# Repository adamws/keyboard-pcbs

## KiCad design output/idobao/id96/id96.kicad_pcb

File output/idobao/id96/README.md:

## idobao/id96

[layout](id96-kle.json) - [PCB](id96.kicad_pcb)

{:loading="lazy"}

[Open in keyboard-layout-editor](http://www.keyboard-layout-editor.com/##@@_x:2.75&c=#777777;&=5,0&_c=#cccccc;&=5,1&=5,2&=5,3&=5,4&=5,5&=5,6&=5,7&=5,8&=11,8&=11,7&=11,5&=11,4&_c=#aaaaaa;&=11,3&=11,6&=11,2&=11,1&=11,0&=6,3;&@_x:2.75&c=#cccccc;&=4,0&=4,1&=4,2&=4,3&=4,4&=4,5&=4,6&=4,7&=4,8&=10,8&=10,7&=10,5&=10,4&_c=#aaaaaa&w:2;&=10,6%0A%0A%0A0,0&_c=#777777;&=10,2&_c=#aaaaaa;&=10,1&=10,0&=6,4;&@_x:2.75&w:1.5;&=3,0&_c=#cccccc;&=3,1&=3,2&=3,3&=3,4&=3,5&=3,6&=3,7&=3,8&=9,8&=9,7&=9,5&=9,4&_w:1.5;&=8,4&=9,6&=9,2&=9,1&_c=#aaaaaa&h:2;&=8,0%0A%0A%0A1,0;&@_x:2.75&c=#777777&w:1.75;&=2,0&_c=#cccccc;&=2,1&=2,2&=2,3&=2,4&=2,5&=2,6&=2,7&=2,8&=8,8&=8,7&=8,5&_c=#777777&w:2.25;&=9,3&_c=#cccccc;&=8,6&=8,2&=8,1;&@_x:2.75&c=#aaaaaa&w:2.25;&=1,0%0A%0A%0A3,0&_c=#cccccc;&=1,2&=1,3&=1,4&=1,5&=1,6&=1,7&=1,8&=7,8&=7,7&=7,5&_c=#aaaaaa&w:1.75;&=7,4%0A%0A%0A5,0&_c=#777777;&=7,3%0A%0A%0A5,0&_c=#cccccc;&=7,6&=7,2&=7,1&_c=#777777&h:2;&=6,0%0A%0A%0A2,0;&@_x:2.75&c=#aaaaaa&w:1.25;&=0,0%0A%0A%0A6,0&_w:1.25;&=0,1%0A%0A%0A6,0&_w:1.25;&=0,2%0A%0A%0A6,0&_c=#cccccc&w:6.25;&=0,6%0A%0A%0A6,0&_c=#aaaaaa;&=0,8%0A%0A%0A6,0&=0,7%0A%0A%0A6,0&=0,5%0A%0A%0A6,0&_c=#777777;&=0,4%0A%0A%0A6,0&=0,3%0A%0A%0A6,0&=6,6%0A%0A%0A4,0&_c=#cccccc;&=6,2%0A%0A%0A4,0&=6,1;&@_x:22.5&y:-5;&=10,3%0A%0A%0A0,1&_c=#aaaaaa;&=10,6%0A%0A%0A0,1;&@_x:21.75;&=9,0%0A%0A%0A1,1;&@_x:21.75;&=8,0%0A%0A%0A1,1;&@_x:0.25&w:1.25;&=1,0%0A%0A%0A3,1&_c=#cccccc;&=1,1%0A%0A%0A3,1&_x:21.0&c=#aaaaaa;&=7,0%0A%0A%0A2,1;&@_x:23.5&c=#777777;&=6,0%0A%0A%0A2,1;&@_x:2.75&y:0.5&c=#aaaaaa&w:1.25;&=0,0%0A%0A%0A6,1&_w:1.25;&=0,1%0A%0A%0A6,1&_w:1.25;&=0,2%0A%0A%0A6,1&_c=#cccccc&w:6.25;&=0,6%0A%0A%0A6,1&_c=#aaaaaa&w:1.5;&=0,8%0A%0A%0A6,1&_w:1.5;&=0,5%0A%0A%0A6,1&_c=#777777;&=0,4%0A%0A%0A6,1&=0,3%0A%0A%0A6,1&_x:0.5&c=#aaaaaa&w:2.75;&=7,4%0A%0A%0A5,1;&@_x:2.75&w:1.25;&=0,0%0A%0A%0A6,2&_w:1.25;&=0,1%0A%0A%0A6,2&_w:1.25;&=0,2%0A%0A%0A6,2&_c=#cccccc&w:6.25;&=0,6%0A%0A%0A6,2&_c=#aaaaaa&w:1.25;&=0,8%0A%0A%0A6,2&_w:1.25;&=0,7%0A%0A%0A6,2&_w:1.25;&=0,4%0A%0A%0A6,2&_w:1.25;&=0,3%0A%0A%0A6,2&_x:0.5&c=#cccccc&w:2;&=6,2%0A%0A%0A4,1;&@_x:2.75&c=#aaaaaa&w:1.5;&=0,0%0A%0A%0A6,3&_w:1.5;&=0,1%0A%0A%0A6,3&_c=#cccccc&w:7;&=0,6%0A%0A%0A6,3&_c=#aaaaaa&w:1.5;&=0,8%0A%0A%0A6,3&_w:1.5;&=0,5%0A%0A%0A6,3&_c=#777777;&=0,4%0A%0A%0A6,3&=0,3%0A%0A%0A6,3;&@_x:2.75&c=#aaaaaa&w:1.5;&=0,0%0A%0A%0A6,4&_w:1.5;&=0,1%0A%0A%0A6,4&_c=#cccccc&w:7;&=0,6%0A%0A%0A6,4&_c=#aaaaaa&w:1.25;&=0,8%0A%0A%0A6,4&_w:1.25;&=0,7%0A%0A%0A6,4&_w:1.25;&=0,4%0A%0A%0A6,4&_w:1.25;&=0,3%0A%0A%0A6,4;&@_x:2.75&w:1.5;&=0,0%0A%0A%0A6,5&_w:1.5;&=0,1%0A%0A%0A6,5&_c=#cccccc&w:7;&=0,6%0A%0A%0A6,5&_c=#aaaaaa;&=0,8%0A%0A%0A6,5&=0,7%0A%0A%0A6,5&=0,5%0A%0A%0A6,5&_c=#777777;&=0,4%0A%0A%0A6,5&=0,3%0A%0A%0A6,5;&@_x:2.75&c=#aaaaaa&w:1.5;&=0,0%0A%0A%0A6,6&=0,1%0A%0A%0A6,6&_w:1.5;&=0,2%0A%0A%0A6,6&_c=#cccccc&w:7;&=0,6%0A%0A%0A6,6&_c=#aaaaaa&w:1.5;&=0,7%0A%0A%0A6,6&=0,4%0A%0A%0A6,6&_w:1.5;&=0,3%0A%0A%0A6,6;&@_x:2.75&w:1.5;&=0,0%0A%0A%0A6,7&=0,1%0A%0A%0A6,7&_w:1.5;&=0,2%0A%0A%0A6,7&_c=#cccccc&w:7;&=0,6%0A%0A%0A6,7&_c=#aaaaaa;&=0,7%0A%0A%0A6,7&=0,5%0A%0A%0A6,7&_c=#777777;&=0,4%0A%0A%0A6,7&=0,3%0A%0A%0A6,7;&@_x:2.75&c=#aaaaaa&w:1.5;&=0,0%0A%0A%0A6,8&=0,1%0A%0A%0A6,8&_w:1.5;&=0,2%0A%0A%0A6,8&_c=#cccccc&w:6;&=0,6%0A%0A%0A6,8&_c=#aaaaaa&w:1.5;&=0,8%0A%0A%0A6,8&_w:1.5;&=0,5%0A%0A%0A6,8&_c=#777777;&=0,4%0A%0A%0A6,8&=0,3%0A%0A%0A6,8;&@_x:2.75&c=#aaaaaa&w:1.5;&=0,0%0A%0A%0A6,9&=0,1%0A%0A%0A6,9&_w:1.5;&=0,2%0A%0A%0A6,9&_c=#cccccc&w:6;&=0,6%0A%0A%0A6,9&_c=#aaaaaa;&=0,8%0A%0A%0A6,9&=0,7%0A%0A%0A6,9&=0,5%0A%0A%0A6,9&_c=#777777;&=0,4%0A%0A%0A6,9&=0,3%0A%0A%0A6,9;&@_x:2.75&c=#aaaaaa&w:1.5;&=0,0%0A%0A%0A6,10&=0,1%0A%0A%0A6,10&_w:1.5;&=0,2%0A%0A%0A6,10&_c=#cccccc&w:6;&=0,6%0A%0A%0A6,10&_c=#aaaaaa&w:1.25;&=0,8%0A%0A%0A6,10&_w:1.25;&=0,7%0A%0A%0A6,10&_w:1.25;&=0,4%0A%0A%0A6,10&_w:1.25;&=0,3%0A%0A%0A6,10)

{:loading="lazy"}

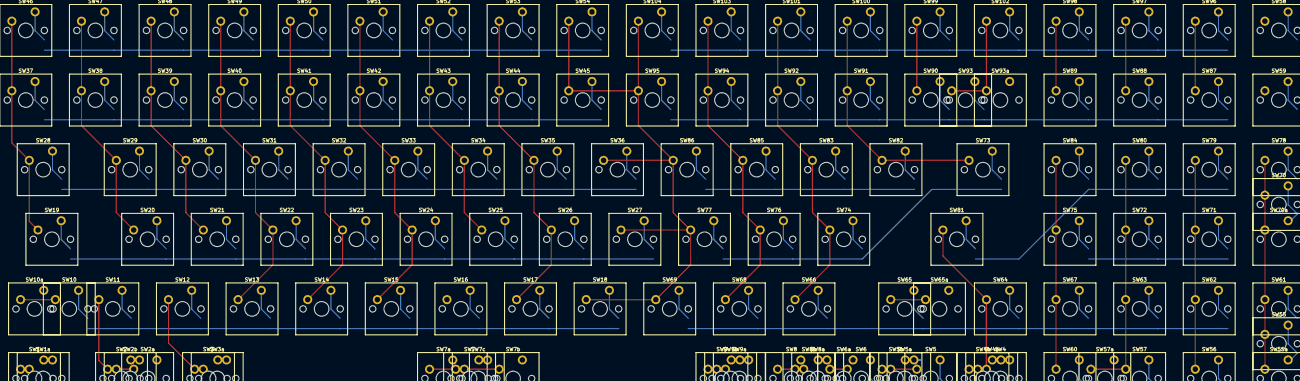
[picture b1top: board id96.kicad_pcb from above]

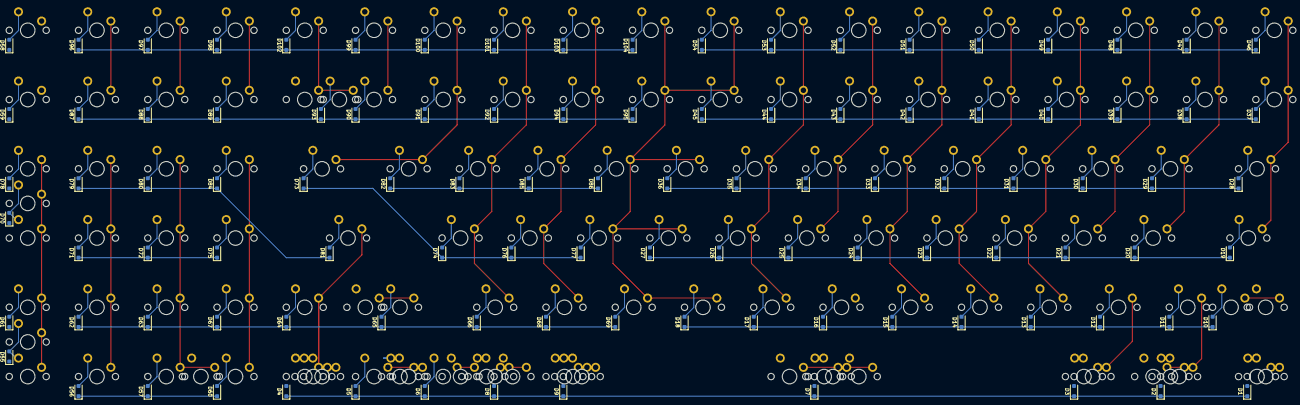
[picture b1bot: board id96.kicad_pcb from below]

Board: 2 copper layers, 230 parts (104 on the bottom side), 125 nets.

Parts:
D1, D2, D3, D4, D5, D6, D7, D8, D9, D10, D11, D12, D13, D14, D15, D16, D17, D18, D19, D20, D21, D22, D23, D24, D25, D26, D27, D28, D29, D30, D31, D32, D33, D34, D35, D36, D37, D38, D39, D40, D41, D42, D43, D44, D45, D46, D47, D48, D49, D50, D51, D52, D53, D54, D55, D56, D57, D58, D59, D60, D61, D62, D63, D64, D65, D66, D67, D68, D69, D70, D71, D72, D73, D74, D75, D76, D77, D78, D79, D80, D81, D82, D83, D84, D85, D86, D87, D88, D89, D90, D91, D92, D93, D94, D95, D96, D97, D98, D99, D100, D101, D102, D103, D104: D_SOD-123F
SW1, SW1a, SW2, SW2a, SW2b, SW3, SW3a, SW4, SW4a, SW4b, SW5, SW5a, SW5b, SW6, SW6a, SW7, SW7a, SW7b, SW7c, SW8, SW8a, SW8b, SW9, SW9a, SW9b, SW10, SW10a, SW11, SW12, SW13, SW14, SW15, SW16, SW17, SW18, SW19, SW20, SW21, SW22, SW23, SW24, SW25, SW26, SW27, SW28, SW29, SW30, SW31, SW32, SW33, SW34, SW35, SW36, SW37, SW38, SW39, SW40, SW41, SW42, SW43, SW44, SW45, SW46, SW47, SW48, SW49, SW50, SW51, SW52, SW53, SW54, SW55, SW55a, SW56, SW57, SW57a, SW58, SW59, SW60, SW61, SW62, SW63, SW64, SW65, SW65a, SW66, SW67, SW68, SW69, SW70, SW70a, SW71, SW72, SW73, SW74, SW75, SW76, SW77, SW78, SW79, SW80, SW81, SW82, SW83, SW84, SW85, SW86, SW87, SW88, SW89, SW90, SW91, SW92, SW93, SW93a, SW94, SW95, SW96, SW97, SW98, SW99, SW100, SW101, SW102, SW103, SW104: SW_Cherry_MX_PCB_1.00u

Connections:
COL0: SW1.1, SW1a.1, SW10.1, SW10a.1, SW19.1, SW28.1, SW37.1, SW46.1, SW55.1, SW55a.1, SW61.1, SW70.1, SW70a.1, SW78.1, SW87.1, SW96.1
COL1: SW2.1, SW2a.1, SW2b.1, SW11.1, SW20.1, SW29.1, SW38.1, SW47.1, SW56.1, SW62.1, SW71.1, SW79.1, SW88.1, SW97.1
COL2: SW3.1, SW3a.1, SW12.1, SW21.1, SW30.1, SW39.1, SW48.1, SW57.1, SW57a.1, SW63.1, SW72.1, SW80.1, SW89.1, SW98.1
COL3: SW4.1, SW4a.1, SW4b.1, SW13.1, SW22.1, SW31.1, SW40.1, SW49.1, SW58.1, SW64.1, SW81.1, SW90.1, SW99.1
COL4: SW5.1, SW5a.1, SW5b.1, SW14.1, SW23.1, SW32.1, SW41.1, SW50.1, SW59.1, SW65.1, SW65a.1, SW73.1, SW82.1, SW91.1, SW100.1
COL5: SW6.1, SW6a.1, SW15.1, SW24.1, SW33.1, SW42.1, SW51.1, SW66.1, SW74.1, SW83.1, SW92.1, SW101.1
COL6: SW7.1, SW7a.1, SW7b.1, SW7c.1, SW16.1, SW25.1, SW34.1, SW43.1, SW52.1, SW60.1, SW67.1, SW75.1, SW84.1, SW93.1, SW93a.1, SW102.1
COL7: SW8.1, SW8a.1, SW8b.1, SW17.1, SW26.1, SW35.1, SW44.1, SW53.1, SW68.1, SW76.1, SW85.1, SW94.1, SW103.1
COL8: SW9.1, SW9a.1, SW9b.1, SW18.1, SW27.1, SW36.1, SW45.1, SW54.1, SW69.1, SW77.1, SW86.1, SW95.1, SW104.1
unnamed: D1.2, SW1.2, SW1a.2
unnamed: D2.2, SW2.2, SW2a.2, SW2b.2
unnamed: D3.2, SW3.2, SW3a.2
unnamed: D4.2, SW4.2, SW4a.2, SW4b.2
unnamed: D5.2, SW5.2, SW5a.2, SW5b.2
unnamed: D6.2, SW6.2, SW6a.2
unnamed: D7.2, SW7.2, SW7a.2, SW7b.2, SW7c.2
unnamed: D8.2, SW8.2, SW8a.2, SW8b.2
unnamed: D9.2, SW9.2, SW9a.2, SW9b.2
unnamed: D10.2, SW10.2, SW10a.2
unnamed: D11.2, SW11.2
unnamed: D12.2, SW12.2
unnamed: D13.2, SW13.2
unnamed: D14.2, SW14.2
unnamed: D15.2, SW15.2
unnamed: D16.2, SW16.2
unnamed: D17.2, SW17.2
unnamed: D18.2, SW18.2
unnamed: D19.2, SW19.2
unnamed: D20.2, SW20.2
unnamed: D21.2, SW21.2
unnamed: D22.2, SW22.2
unnamed: D23.2, SW23.2
unnamed: D24.2, SW24.2
unnamed: D25.2, SW25.2
unnamed: D26.2, SW26.2
unnamed: D27.2, SW27.2
unnamed: D28.2, SW28.2
unnamed: D29.2, SW29.2
unnamed: D30.2, SW30.2
unnamed: D31.2, SW31.2
unnamed: D32.2, SW32.2
unnamed: D33.2, SW33.2
unnamed: D34.2, SW34.2
unnamed: D35.2, SW35.2
unnamed: D36.2, SW36.2
unnamed: D37.2, SW37.2
unnamed: D38.2, SW38.2
unnamed: D39.2, SW39.2
unnamed: D40.2, SW40.2
unnamed: D41.2, SW41.2
unnamed: D42.2, SW42.2
unnamed: D43.2, SW43.2
unnamed: D44.2, SW44.2
unnamed: D45.2, SW45.2
unnamed: D46.2, SW46.2
unnamed: D47.2, SW47.2
unnamed: D48.2, SW48.2
unnamed: D49.2, SW49.2
unnamed: D50.2, SW50.2
unnamed: D51.2, SW51.2
unnamed: D52.2, SW52.2
unnamed: D53.2, SW53.2
unnamed: D54.2, SW54.2
unnamed: D55.2, SW55.2, SW55a.2
unnamed: D56.2, SW56.2
unnamed: D57.2, SW57.2, SW57a.2
unnamed: D58.2, SW58.2
unnamed: D59.2, SW59.2
unnamed: D60.2, SW60.2
unnamed: D61.2, SW61.2
unnamed: D62.2, SW62.2
unnamed: D63.2, SW63.2
unnamed: D64.2, SW64.2
unnamed: D65.2, SW65.2, SW65a.2
unnamed: D66.2, SW66.2
unnamed: D67.2, SW67.2
unnamed: D68.2, SW68.2
unnamed: D69.2, SW69.2
unnamed: D70.2, SW70.2, SW70a.2
unnamed: D71.2, SW71.2
unnamed: D72.2, SW72.2
unnamed: D73.2, SW73.2
unnamed: D74.2, SW74.2
unnamed: D75.2, SW75.2
unnamed: D76.2, SW76.2
unnamed: D77.2, SW77.2
unnamed: D78.2, SW78.2
unnamed: D79.2, SW79.2
unnamed: D80.2, SW80.2
unnamed: D81.2, SW81.2
unnamed: D82.2, SW82.2
unnamed: D83.2, SW83.2
unnamed: D84.2, SW84.2
unnamed: D85.2, SW85.2
unnamed: D86.2, SW86.2
unnamed: D87.2, SW87.2
unnamed: D88.2, SW88.2
unnamed: D89.2, SW89.2
unnamed: D90.2, SW90.2
unnamed: D91.2, SW91.2
unnamed: D92.2, SW92.2
unnamed: D93.2, SW93.2, SW93a.2
unnamed: D94.2, SW94.2
unnamed: D95.2, SW95.2
unnamed: D96.2, SW96.2
unnamed: D97.2, SW97.2
unnamed: D98.2, SW98.2
unnamed: D99.2, SW99.2
unnamed: D100.2, SW100.2
unnamed: D101.2, SW101.2
unnamed: D102.2, SW102.2
unnamed: D103.2, SW103.2
unnamed: D104.2, SW104.2
ROW0: D1.1, D2.1, D3.1, D4.1, D5.1, D6.1, D7.1, D8.1, D9.1
ROW1: D10.1, D11.1, D12.1, D13.1, D14.1, D15.1, D16.1, D17.1, D18.1
ROW2: D19.1, D20.1, D21.1, D22.1, D23.1, D24.1, D25.1, D26.1, D27.1
ROW3: D28.1, D29.1, D30.1, D31.1, D32.1, D33.1, D34.1, D35.1, D36.1
ROW4: D37.1, D38.1, D39.1, D40.1, D41.1, D42.1, D43.1, D44.1, D45.1
ROW5: D46.1, D47.1, D48.1, D49.1, D50.1, D51.1, D52.1, D53.1, D54.1
ROW6: D55.1, D56.1, D57.1, D58.1, D59.1, D60.1
ROW7: D61.1, D62.1, D63.1, D64.1, D65.1, D66.1, D67.1, D68.1, D69.1
ROW8: D70.1, D71.1, D72.1, D73.1, D74.1, D75.1, D76.1, D77.1
ROW9: D78.1, D79.1, D80.1, D81.1, D82.1, D83.1, D84.1, D85.1, D86.1
ROW10: D87.1, D88.1, D89.1, D90.1, D91.1, D92.1, D93.1, D94.1, D95.1
ROW11: D96.1, D97.1, D98.1, D99.1, D100.1, D101.1, D102.1, D103.1, D104.1
